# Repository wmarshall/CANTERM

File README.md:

# CANTERM

A single SKU for FRC teams providing the following features:

1. Fixed mounting junction for CAN connections, compatible with the 0.1" pitch connector of your choice (Molex SL footprints on silkscreen)
2. Solder pads and test points for 22AWG wire
3. 3 connection points - create short stubs out to individual devices and have a passthrough
4. Switchable termination - every junction can be a termination point!
5. Mountable to standard 0.5"x#10 FRC pitch grid

## Images

Apologies for the flux slime + sharpied out silkscreen where I labeled things backwards in rev 1.

## How to use

### Mounting

I recommend a fixed connection to a hard surface, with padding behind to prevent the through-hole pins from making electrical contact.

[Here](https://cad.onshape.com/documents/4bac7b549ef6666940699ce5/w/56cf0a0da1905853099fed6a/e/bae3fd6128463807bfcfc51d?renderMode=0&uiState=67784d31596e316774ed116e) is a WIP Case CAD that accomplishes this.

### As a junction

1. Connect your input connector to one set of contacts
2. Connect your output connector to a second set of contacts
3. Set the termination switch to `OFF` (away from `ON`)

#### Debugging

Have a break in your CAN chain but don't know where it is? Use the switchable termination feature to find out where

1. Disconnect your output connector
2. Set the termination switch to `ON`
3. You should now have a properly terminated network on the input side. If problems persist, the break is on that side. If they don't the break is on the output side.
4. Repeatedly bisect the network until the problem is found
5. Reconnect connectors and set the termination back to `OFF`

### As a terminator

1. Connect your input connector to one set of contacts
3. Set the termination switch to `ON`

### As a junction with a stub

1. Connect your input connector to one set of contacts
2. Connect your output connector to a second set of contacts
3. Connect your stub connector to the third set of contacts
3. Set the termination switch to `OFF` (away from `ON`)

### As a terminator (soldered)

1. Strip ~3/8" of each of your CAN wires.
2. Feed them through the test points
3. Solder to the contact patches on the back, making sure to also solder through the test points
4. Trim excess wire.
5. Set the termination switch to `ON`

## BOM

1. 3x `Molex_SL_171971-0003` (only 2 needed if not making stubs)
2. 1x 120 ohm 0805 SMT resistor
3. 1x SPST 0.1" pitch SMT DIP switch (DS04-254-2-01BK-SMT is what I used)

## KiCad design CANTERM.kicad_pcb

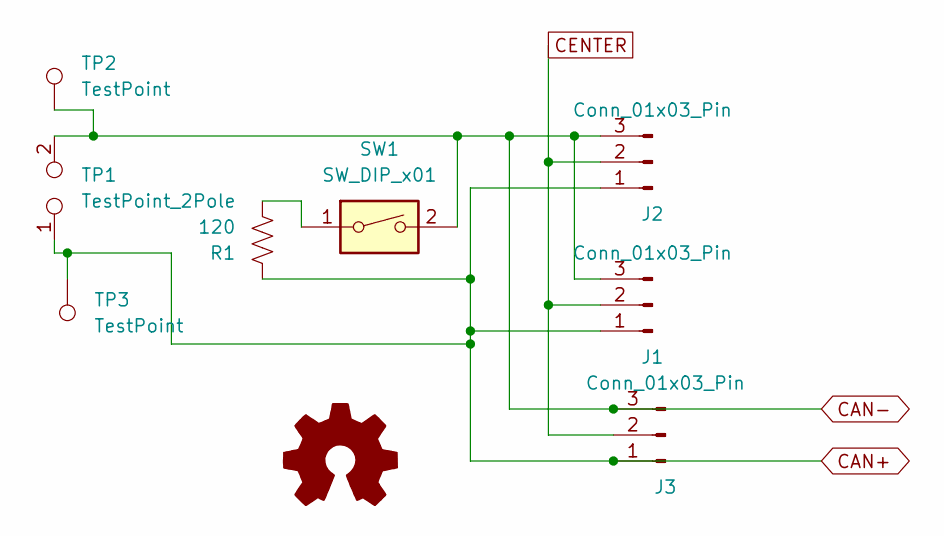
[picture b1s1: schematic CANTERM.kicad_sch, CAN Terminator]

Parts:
J1, J2, J3: Conn_01x03_Pin; Molex_SL_171971-0003_1x03_P2.54mm_Vertical
R1: 120; R_0805_2012Metric
SW1: SW_DIP_x01; SW_DS04-254-2-01BK-SMT
TP1: TestPoint_2Pole; TestPoint_2Pads_Pitch2.54mm_Drill0.8mm
TP2, TP3: TestPoint; TestPoint_Pad_D2.5mm

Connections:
CAN+: J1.1, J2.1, J3.1, R1.1, TP1.1, TP3.1
CAN-: J1.3, J2.3, J3.3, SW1.2, TP1.2, TP2.1
CENTER: J1.2, J2.2, J3.2
unnamed: R1.2, SW1.1

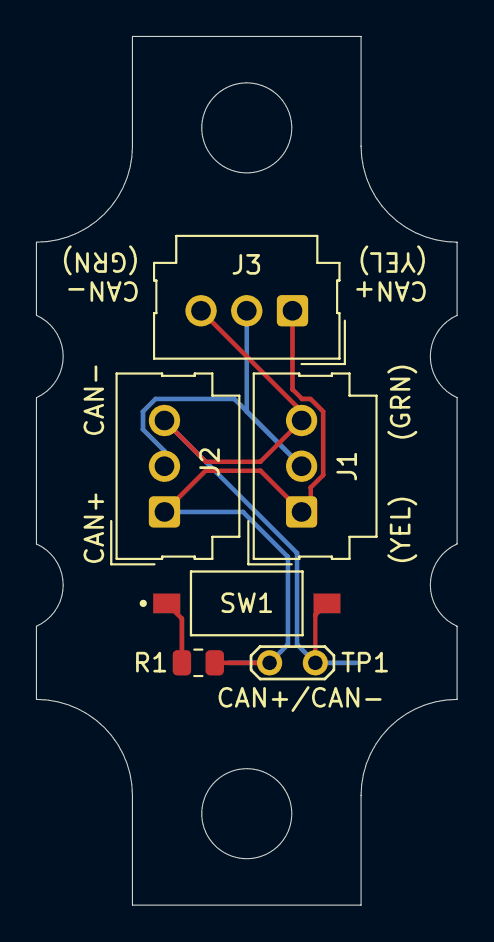
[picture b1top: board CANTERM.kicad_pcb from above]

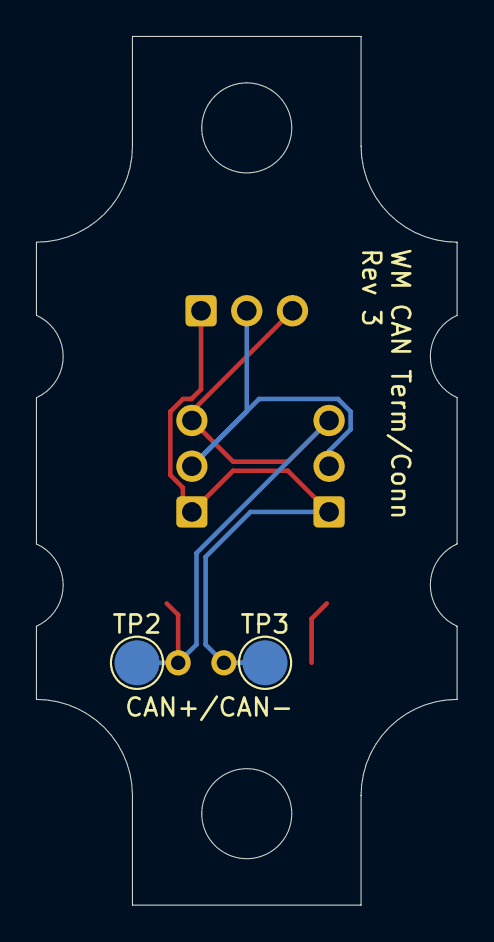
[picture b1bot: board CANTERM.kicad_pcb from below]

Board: 2 copper layers, 23.4 x 48.3 mm, 10 parts (2 on the bottom side), 4 nets.

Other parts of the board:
M1, M2: MountingHole_10

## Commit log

2024-12-10 3rd connector footprint for stub
2024-12-10 remove OSHW logo since I'm not compliant yet
2025-01-03 wider tracks
2025-01-03 initial release
2025-01-03 images forgotten
2025-01-03 images are jpg
2025-01-03 add license
2025-01-23 slightly shrink board so it fits _inside_ the space envelope
2025-01-23 add STEP
2025-01-28 crying, correctly labeled pins
